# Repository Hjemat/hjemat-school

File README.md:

# hjemat-school

-------------------------
Made by
Signe Rhea Grau Kristensen
Morten Nissen

For our electronics exam in Teksnik Gymnasium Sønderborg, May 2016

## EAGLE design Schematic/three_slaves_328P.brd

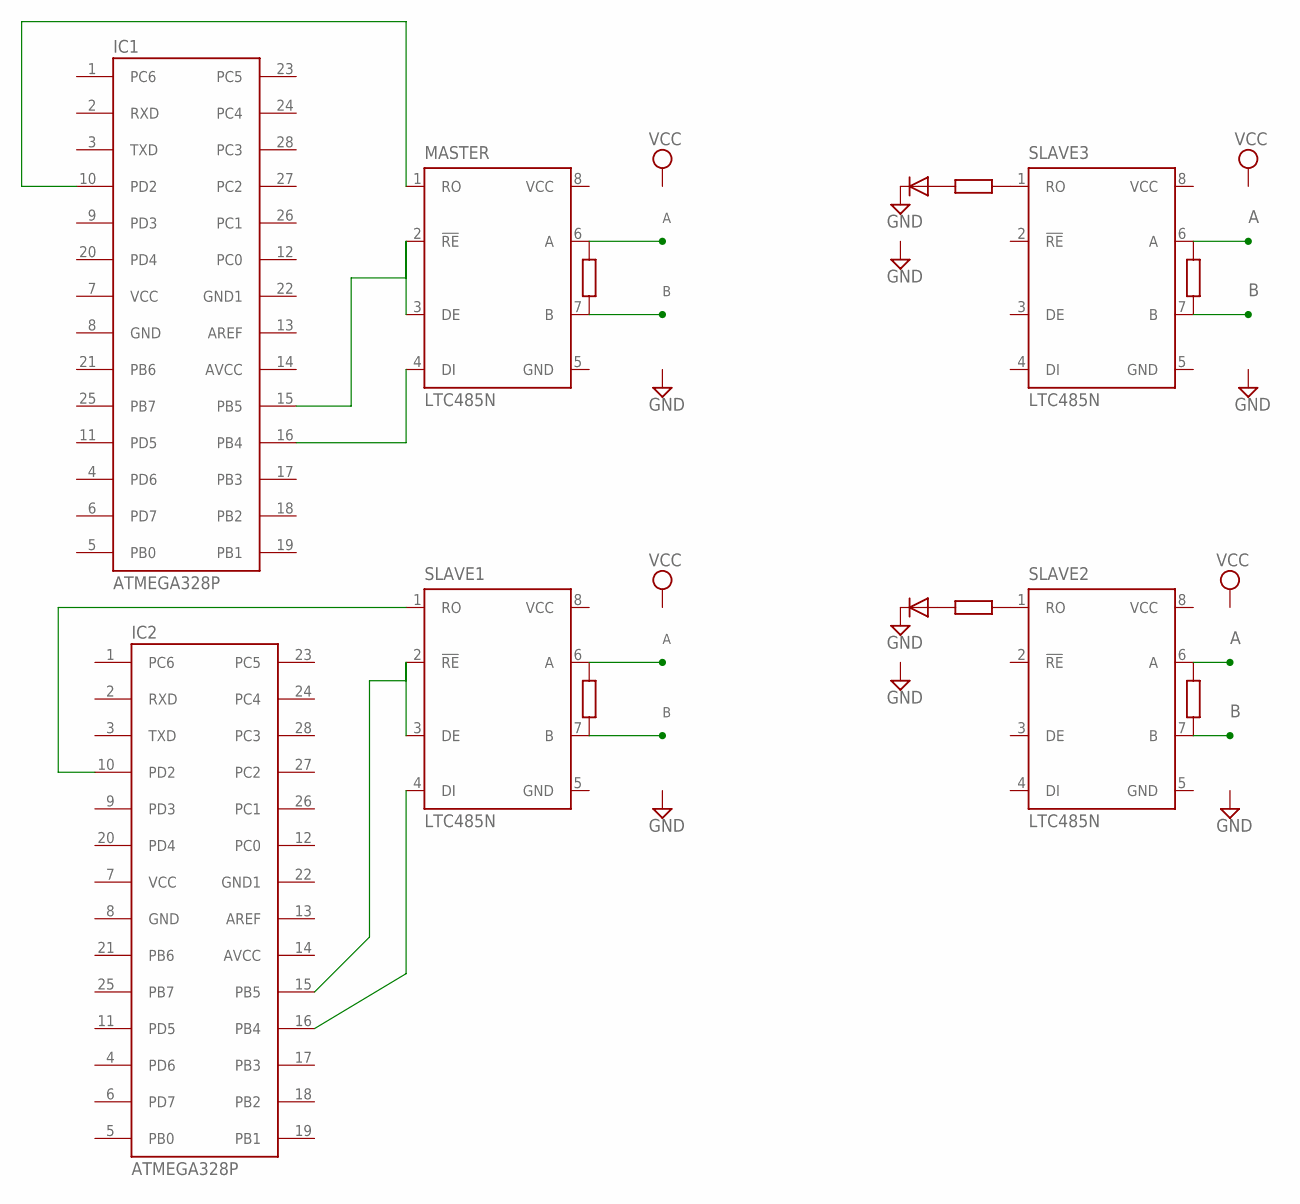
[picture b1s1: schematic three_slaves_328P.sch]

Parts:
D2, D3: 1N4004; DO41-10
IC1, IC2: ATMEGA328P; DIL28-3
MASTER: LTC485N; DIL08
SLAVE1, SLAVE2, SLAVE3: LTC485N; DIL08

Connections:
A: MASTER.6 (A), SLAVE1.6 (A), SLAVE2.6 (A), SLAVE3.6 (A)
B: MASTER.7 (B), SLAVE1.7 (B), SLAVE2.7 (B), SLAVE3.7 (B)
GND: D2.C, D3.C, IC1.8 (GND), IC2.8 (GND)
GND1: IC1.22 (GND1), IC2.22 (GND1)
unnamed: IC1.15 (PB5), MASTER.2 (!RE), MASTER.3 (DE)
unnamed: IC1.16 (PB4), MASTER.4 (DI)
unnamed: IC1.10 (PD2), MASTER.1 (RO)
unnamed: IC2.15 (PB5), SLAVE1.2 (!RE), SLAVE1.3 (DE)
unnamed: IC2.16 (PB4), SLAVE1.4 (DI)
unnamed: IC2.10 (PD2), SLAVE1.1 (RO)
VCC: IC1.7 (VCC), IC2.7 (VCC)

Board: 2 copper layers, 8 parts (0 on the bottom side), 11 nets, no tracks yet.

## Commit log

2016-04-12 migrate from old rep
2016-04-12 Added logo files
2016-04-12 Added hexidecimal codes
2016-04-13 Updated protocol spec
2016-04-13 updated them
2016-04-29 328P and rs485 schematic
2016-04-29 Master with Voltage shifting
2016-04-29 removed lock
2016-05-02 Added files via upload
    Added Sprint template
2016-05-03 GPIO changes
2016-05-03 Added files via upload
    Added Rasberry Pi for sprint to print out.
2016-05-04 Template for reciever
2016-05-04 Added files via upload
2016-05-04 Reciever Temperature
2016-05-04 Reciever Light
2016-05-04 Temp schematic
2016-05-09 Added specs for pairing
2016-05-11 added templates
2016-05-11 cleanup
2016-05-12 Gør klar til eksamen
2022-04-07 build pdf
